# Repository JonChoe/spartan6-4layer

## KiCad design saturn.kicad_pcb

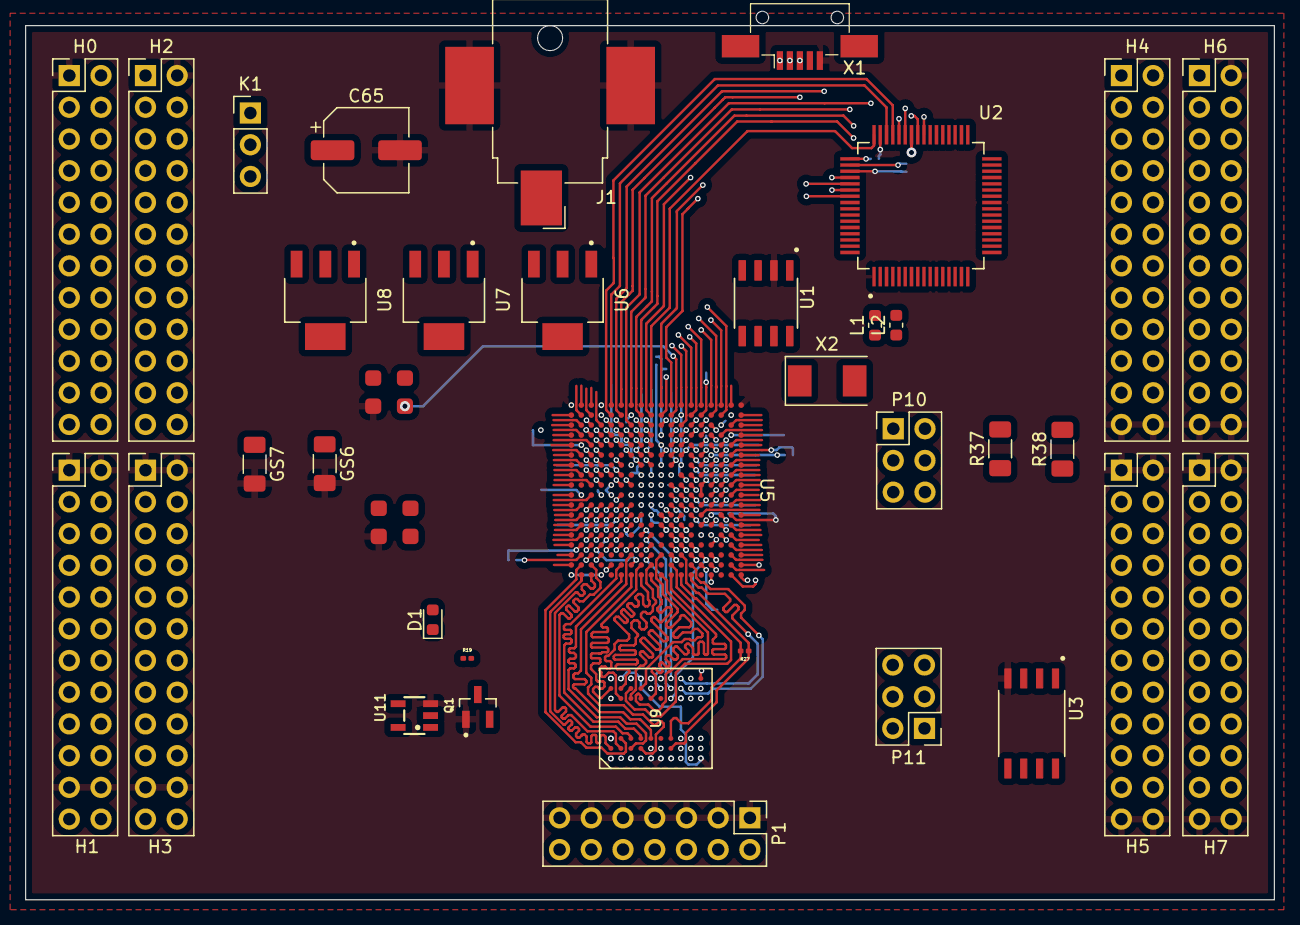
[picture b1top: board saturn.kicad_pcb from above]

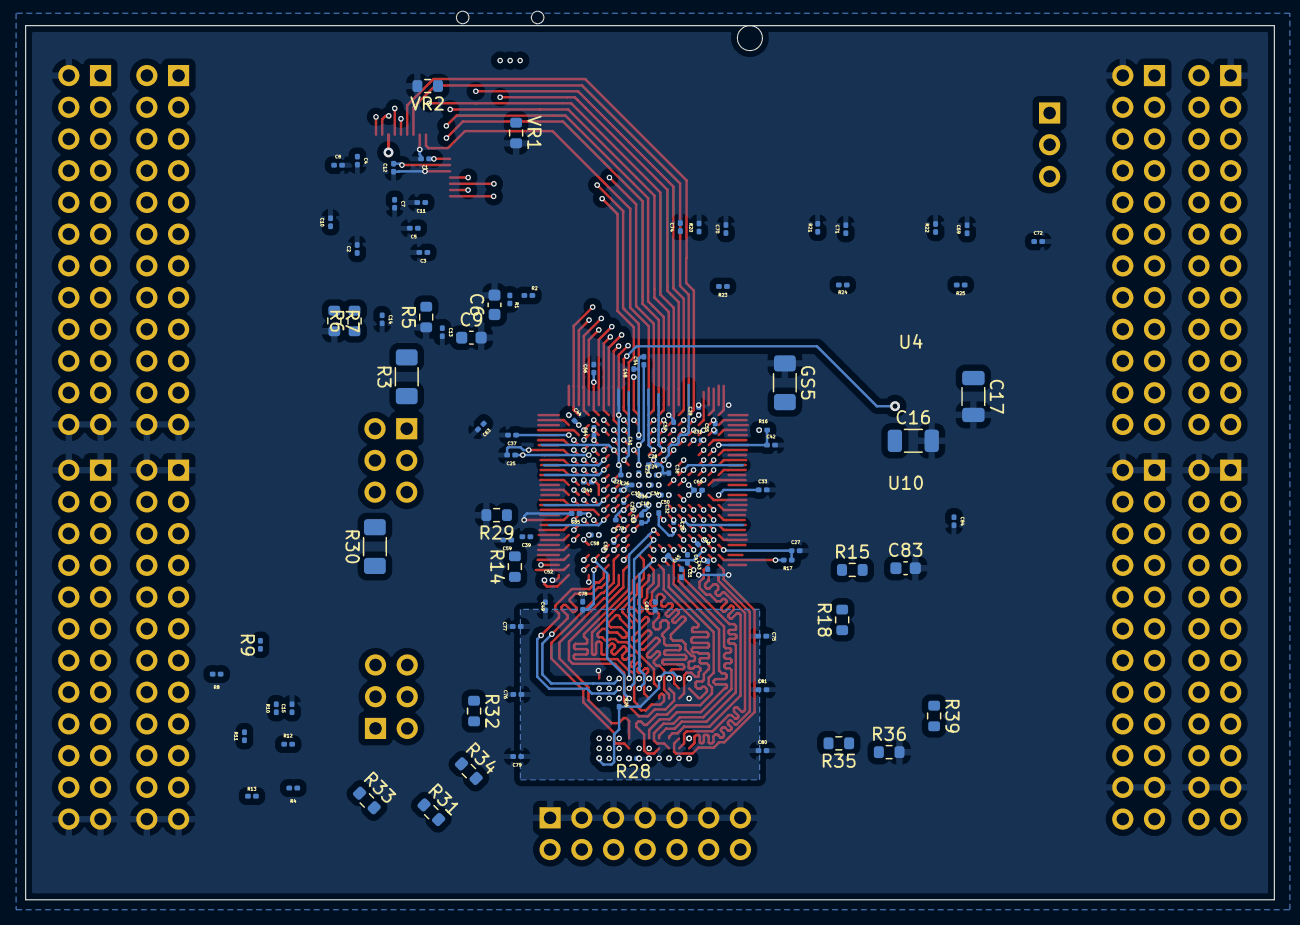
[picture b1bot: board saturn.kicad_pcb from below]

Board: 4 copper layers, 100.0 x 70.0 mm, 153 parts (116 on the bottom side), 261 nets.

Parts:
C1, C2, C3, C4, C5, C7, C8, C10, C11, C12, C13, C14, C15, C72, C73, C74, C75, C76, C77, C78, C79, C80, C81, C82: 0.1uF; C_0201_0603Metric
C6, C9: 22pF; C_0603_1608Metric
C16, C17: DNP; C_1206_3216Metric
C18, C19, C20, C21, C22, C23, C24, C25, C26, C27, C28, C29, C30, C31, C32, C33, C34, C35, C36, C37, C38, C39, C40, C41, C42, C43, C44, C45, C46, C47, C48, C49, C50, C51, C52, C53, C54, C55, C56, C57, C58, C59, C60, C63, C64, C84: 0.01uF; C_0201_0603Metric
C65: 47uF; CP_Elec_6.3x7.7
C69, C70, C71: 10uF; C_0201_0603Metric
C83: 15pF; C_0603_1608Metric
D1: LED; LED_0603_1608Metric
GS5, GS6, GS7: PAD; R_1206_3216Metric_Pad1.30x1.75mm_HandSolder
H0, H1, H2, H3, H4, H5, H6, H7: header-2x12-2.54; PinHeader_2x12_P2.54mm_Vertical
J1: DC_barrel; BarrelJack_CUI_PJ-036AH-SMT_Horizontal
K1: VBUS_VCCIN; PinHeader_1x03_P2.54mm_Vertical
L1, L2: INDUCTOR; L_0603_1608Metric
P1: JTAG-14PIN; PinHeader_2x07_P2.54mm_Vertical
P10, P11: PLUG-6-PIN; PinHeader_2x03_P2.54mm_Vertical
Q1: NPN; SOT95P237X125-3N
R1, R10, R11, R13, R16: 10K; R_0201_0603Metric
R2: 2K2; R_0201_0603Metric
R3, R30, R37, R38: DNP; R_1206_3216Metric_Pad1.30x1.75mm_HandSolder
R4, R8, R9, R12, R21: 0R; R_0201_0603Metric
R5: 12K; R_0603_1608Metric
R6: 4K7; R_0603_1608Metric
R7, R15, R35, R36: 10K; R_0603_1608Metric
R14: 4.7K; R_0603_1608Metric
R17, R19, R28: 4.7K; R_0201_0603Metric
R18: 1K; R_0603_1608Metric
R20: 330R; R_0201_0603Metric
R22, R26, R27: 100R; R_0201_0603Metric
R23, R24, R25: 220R; R_0201_0603Metric
R29: 100R; R_0603_1608Metric
R31, R32, R33, R34: 0R; R_0603_1608Metric
R39: 2.2K; R_0603_1608Metric
U1: 93LC46; SOIC127P600X175-8N
U2: FT2232H; QFP50P1200X1200X160-64N
U3: N25Q128; SOP127P790X216-8N
U4, U10: FXO-HC536R
U5: SPARTAN6-CSG324; CSG324
U6, U7, U8: LM1117-ADJ; SOT230P700X180-4N
U9: MT46H32M16LF; VFBGA60
U11: 74LVC1GU04; SOT23-5
VR1, VR2: VARIABLE_RESISTOR; R_0603_1608Metric
X1: USBMINI; USB_Mini-B_AdamTech_MUSB-B5-S-VT-TSMT-1_SMD_Vertical
X2: 12MHz; Crystal_SMD_0603-2Pin_6.0x3.5mm

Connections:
/FTDI2232H/74LV-A: R35.1, R36.1, U2.24 (ADBUS7), U11.2 (A)
/FTDI2232H/C: R4.2, U3.6 (C)
/FTDI2232H/D: R12.2, U3.5 (D)
/FTDI2232H/DM: U2.7 (DM), VR1.1, X1.2 (D-)
/FTDI2232H/DO: R1.2, R2.1, U1.1 (DO)
/FTDI2232H/DP: U2.8 (DP), VR2.1, X1.3 (D+)
/FTDI2232H/EECLK: R38.2, U1.4 (CLK), U2.62 (EECLK)
/FTDI2232H/EECS: R37.2, U1.5 (CS), U2.63 (EECS)
/FTDI2232H/EEDATA: R2.2, U1.3 (DI), U2.61 (EEDATA)
/FTDI2232H/OSCI: C6.1, U2.2 (OSCI), X2.1
/FTDI2232H/OSCO: C9.1, U2.3 (OSCO), X2.2
/FTDI2232H/Q: R9.1, U3.2 (Q)
/FTDI2232H/REF: R5.2, U2.6 (REF)
/FTDI2232H/TCK: P1.6, P11.2, P11.4, R31.1, R31.2, U2.16 (ADBUS0), U5.A17 (TCK)
/FTDI2232H/TDI: P1.10, P10.3, P10.5, R32.1, R32.2, U2.17 (ADBUS1), U5.D15 (TDI)
/FTDI2232H/TDO: P1.8, P10.2, P10.4, R34.1, R34.2, U2.18 (ADBUS2), U5.D16 (TDO)
/FTDI2232H/TMS: P1.4, P11.3, P11.5, R33.1, R33.2, U2.19 (ADBUS3), U5.B18 (TMS)
/FTDI2232H/U1-CS: P11.6, R8.2, U5.V3 (IO_L65N_CSO_B_2)
/FTDI2232H/U1-D0: U2.38 (BDBUS0), U5.L17 (IO_L46P_FCS_B_M1DQ2_1)
/FTDI2232H/U1-D1: U2.39 (BDBUS1), U5.L18 (IO_L46N_FOE_B_M1DQ3_1)
/FTDI2232H/U1-D2: U2.40 (BDBUS2), U5.M16 (IO_L47P_FWE_B_M1DQ0_1)
/FTDI2232H/U1-D3: U2.41 (BDBUS3), U5.M18 (IO_L47N_LDC_M1DQ1_1)
/FTDI2232H/U1-D4: U2.43 (BDBUS4), U5.N17 (IO_L48P_HDC_M1DQ8_1)
/FTDI2232H/U1-D5: U2.44 (BDBUS5), U5.N18 (IO_L48N_M1DQ9_1)
/FTDI2232H/U1-D6: U2.45 (BDBUS6), U5.P17 (IO_L49P_M1DQ10_1)
/FTDI2232H/U1-D7: U2.46 (BDBUS7), U5.P18 (IO_L49N_M1DQ11_1)
/FTDI2232H/U1-RD#: U2.53 (BCBUS2), U5.J18 (IO_L44N_A2_M1DQ7_1)
/FTDI2232H/U1-RXF#: U2.48 (BCBUS0), U5.K18 (IO_L45N_A0_M1LDQSN_1)
/FTDI2232H/U1-SCK: P11.1, R4.1, U5.R15 (IO_L1P_CCLK_2)
/FTDI2232H/U1-SDI: P10.1, R3.1, R9.2, U5.R13 (IO_L3P_D0_DIN_MISO_MISO1_2)
/FTDI2232H/U1-SDO: P10.6, R12.1, R30.2, U5.T13 (IO_L3N_MOSI_CSI_B_MISO0_2)
/FTDI2232H/U1-SIWUB: U2.55 (BCBUS4), U5.H18 (IO_L43N_GCLK4_M1DQ5_1)
/FTDI2232H/U1-TXE#: U2.52 (BCBUS1), U5.K17 (IO_L45P_A1_M1LDQS_1)
/FTDI2232H/U1-WR#: U2.54 (BCBUS3), U5.J16 (IO_L44P_A3_M1DQ6_1)
/FTDI2232H/VCC1V8: C1.1, C2.1, C3.1, C4.1, U2.12 (VCORE), U2.37 (VCORE), U2.49 (VREGOUT), U2.64 (VCORE)
/FTDI2232H/VPHY: C13.1, L1.2, U2.4 (VPHY)
/FTDI2232H/VPLL: C14.1, L2.2, U2.9 (VPLL)
/FTDI2232H/~HOLD: R13.2, U3.7 (~HOLD)
/FTDI2232H/~RESET: R6.2, R7.1, U2.14 (~RESET)
/FTDI2232H/~S: R8.1, R11.2, U3.1 (~S)
/FTDI2232H/~W: R10.2, U3.3 (~W)
/FTDI-AC0: H4.1, U2.26 (ACBUS0)
/FTDI-AC1: H4.2, U2.27 (ACBUS1)
/FTDI-AC2: H4.3, U2.28 (ACBUS2)
/FTDI-AC3: H4.4, U2.29 (ACBUS3)
/FTDI-AC4: H4.5, U2.30 (ACBUS4)
/FTDI-AC5: H4.6, U2.32 (ACBUS5)
/FTDI-AC6: H4.7, U2.33 (ACBUS6)
/FTDI-AC7: H4.8, U2.34 (ACBUS7)
/GPIOS/GPIO-N1: H2.3, U5.K14 (IO_L39N_M10DT_1)
/GPIOS/GPIO-N2: H0.3, U5.G13 (IO_L32N_A16_M1A9_1)
/GPIOS/GPIO-N3: H2.5, U5.H14 (IO_L36N_A8_M1BA1_1)
/GPIOS/GPIO-N4: H0.5, U5.H16 (IO_L37N_A6_M1A1_1)
/GPIOS/GPIO-N6: H0.7, U5.G14 (IO_L30N_A20_M1A11_1)
/GPIOS/GPIO-N7: H2.7, U5.G18 (IO_L38N_A4_M1CLKN_1)
/GPIOS/GPIO-N8: H0.9, U5.F16 (IO_L1N_A24_VREF_1)
/GPIOS/GPIO-N9: H2.9, U5.F18 (IO_L35N_A10_M1A2_1)
/GPIOS/GPIO-N10: H0.11, U5.E18 (IO_L33N_A14_M1A4_1)
/GPIOS/GPIO-N11: H2.11, U5.D18 (IO_L31N_A18_M1A12_1)
/GPIOS/GPIO-N12: H0.13, U5.C18 (IO_L29N_A22_M1A14_1)
/GPIOS/GPIO-N13: H6.4, U5.K13 (IO_L34N_A12_M1BA2_1)
/GPIOS/GPIO-N20: H6.6, U5.M13 (IO_L61N_1)
/GPIOS/GPIO-N21: H4.12, U5.K16 (IO_L41N_GCLK8_M1CASN_1)
/GPIOS/GPIO-N22: H6.8, U5.N14 (IO_L53N_VREF_1)
/GPIOS/GPIO-N23: H6.12, U5.N16 (IO_L50N_M1UDQSN_1)
/GPIOS/GPIO-N24: H6.10, U5.L16 (IO_L42N_GCLK6_TRDY1_M1LDM_1)
/GPIOS/GPIO-N25: H6.14, U5.P16 (IO_L74N_DOUT_BUSY_1)
/GPIOS/GPIO-N26: H4.10, U5.L13 (IO_L40N_GCLK10_M1A6_1)
/GPIOS/GPIO-N27: H4.14, U5.T18 (IO_L51N_M1DQ13_1)
/GPIOS/GPIO-N28: H6.16, U5.U18 (IO_L52N_M1DQ15_1)
/GPIOS/GPIO-N29: H2.13, U5.A16 (IO_L66N_SCP0_0)
/GPIOS/GPIO-N30: H0.15, U5.A15 (IO_L64N_SCP4_0)
/GPIOS/GPIO-N31: H2.15, U5.C14 (IO_L65N_SCP2_0)
/GPIOS/GPIO-N32: H0.17, U5.A14 (IO_L62N_VREF_0)
/GPIOS/GPIO-N33: H2.17, U5.E13 (IO_L63N_SCP6_0)
/GPIOS/GPIO-N34: H0.19, U5.A13 (*IO_L50N_0)
/GPIOS/GPIO-N35: H2.19, U5.E12 (IO_L51N_0)
/GPIOS/GPIO-N36: H0.21, U5.C12 (*IO_L47N_0)
/GPIOS/GPIO-N37: H2.21, U5.A12 (IO_L41N_0)
/GPIOS/GPIO-N38: H0.23, U5.E11 (*IO_L42N_0)
/GPIOS/GPIO-N39: H1.3, U5.F10 (*IO_L40N_0)
/GPIOS/GPIO-N40: H2.23, U5.C11 (IO_L36N_GCLK14_0)
/GPIOS/GPIO-N41: H3.3, U5.A11 (IO_L39N_0)
/GPIOS/GPIO-N42: H1.5, U5.A10 (IO_L37N_GCLK12_0)
/GPIOS/GPIO-N43: H3.5, U5.F9 (IO_L38N_VREF_0)
/GPIOS/GPIO-N44: H1.7, U5.C9 (IO_L34N_GCLK18_0)
/GPIOS/GPIO-N45: H3.7, U5.A9 (IO_L35N_GCLK16_0)
/GPIOS/GPIO-N46: H1.9, U5.F8 (*IO_L32N_0)
/GPIOS/GPIO-N47: H3.9, U5.E8 (*IO_L9N_0)
/GPIOS/GPIO-N48: H1.11, U5.C8 (IO_L11N_0)
/GPIOS/GPIO-N49: H3.11, U5.A8 (IO_L33N_0)
/GPIOS/GPIO-N50: H1.13, U5.E6 (*IO_L7N_0)
/GPIOS/GPIO-N51: H3.13, U5.A7 (IO_L10N_0)
/GPIOS/GPIO-N52: H1.15, U5.A6 (IO_L8N_VREF_0)
/GPIOS/GPIO-N53: H3.15, U5.C6 (IO_L3N_0)
/GPIOS/GPIO-N54: H1.17, U5.A5 (IO_L6N_0)
/GPIOS/GPIO-N55: H3.17, U5.A4 (IO_L5N_0)
/GPIOS/GPIO-N56: H1.19, U5.A3 (IO_L4N_0)
/GPIOS/GPIO-N57: H3.19, U5.A2 (IO_L2N_0)
/GPIOS/GPIO-N58: H4.16, U5.V16 (IO_L2N_CMPMOSI_2)
/GPIOS/GPIO-N59: H6.18, U5.V15 (*IO_L5N_2)
/GPIOS/GPIO-N60: H4.18, U5.V14 (IO_L12N_D2_MISO3_2)
/GPIOS/GPIO-N61: H6.20, U5.V13 (IO_L14N_D12_2)
/GPIOS/GPIO-N62: H4.20, U5.V12 (*IO_L19N_2)
/GPIOS/GPIO-N63: H6.22, U5.N11 (*IO_L15N_2)
/GPIOS/GPIO-N64: H4.22, U5.T11 (IO_L16N_VREF_2)
/GPIOS/GPIO-N65: H7.4, U5.V11 (IO_L23N_2)
/GPIOS/GPIO-N66: H5.4, U5.P11 (*IO_L20N_2)
/GPIOS/GPIO-N67: H7.6, U5.N9 (*IO_L22N_2)
/GPIOS/GPIO-N68: H5.6, U5.T10 (IO_L29N_GCLK2_2)
/GPIOS/GPIO-N69: H7.8, U5.T8 (IO_L31N_GCLK30_D15_2)
/GPIOS/GPIO-N70: H5.8, U5.V9 (IO_L32N_GCLK28_2)
/GPIOS/GPIO-N71: H7.10, U5.N8 (*IO_L40N_2)
/GPIOS/GPIO-N72: H5.10, U5.P8 (*IO_L44N_2)
/GPIOS/GPIO-N73: H7.12, U5.V8 (IO_L41N_VREF_2)
/GPIOS/GPIO-N74: H7.14, U5.P7 (*IO_L47N_2)
/GPIOS/GPIO-N75: H5.12, U5.V7 (IO_L43N_2)
/GPIOS/GPIO-N76: H5.14, U5.T7 (IO_L46N_2)
/GPIOS/GPIO-N77: H7.16, U5.V6 (IO_L45N_2)
/GPIOS/GPIO-N78: H5.16, U5.P6 (IO_L64N_D9_2)
/GPIOS/GPIO-N79: H5.18, U5.T5 (IO_L48N_RDWR_B_VREF_2)
/GPIOS/GPIO-N80: H7.18, U5.V5 (IO_L49N_D4_2)
/GPIOS/GPIO-N81: H7.20, U5.V4 (IO_L63N_2)
/GPIOS/GPIO-N82: H5.20, U5.T3 (IO_L62N_D6_2)
/GPIOS/GPIO-P1: H2.4, U5.J13 (IO_L39P_M1A3_1)
/GPIOS/GPIO-P2: H0.4, U5.H12 (IO_L32P_A17_M1A8_1)
/GPIOS/GPIO-P3: H2.6, U5.H13 (IO_L36P_A9_M1BA0_1)
/GPIOS/GPIO-P4: H0.6, U5.H15 (IO_L37P_A7_M1A0_1)
/GPIOS/GPIO-P6: H0.8, U5.F14 (IO_L30P_A21_M1RESET_1)
/GPIOS/GPIO-P7: H2.8, U5.G16 (IO_L38P_A5_M1CLK_1)
/GPIOS/GPIO-P8: H0.10, U5.F15 (IO_L1P_A25_1)
/GPIOS/GPIO-P9: H2.10, U5.F17 (IO_L35P_A11_M1A7_1)
/GPIOS/GPIO-P10: H0.12, U5.E16 (IO_L33P_A15_M1A10_1)
/GPIOS/GPIO-P11: H2.12, U5.D17 (IO_31P_A19_M1CKE_1)
/GPIOS/GPIO-P12: H0.14, U5.C17 (IO_L29P_A23_M1A13_1)
/GPIOS/GPIO-P13: H6.3, U5.K12 (IO_L34P_A13_M1WE_1)
/GPIOS/GPIO-P20: H6.5, U5.L14 (IO_L61P_1)
/GPIOS/GPIO-P21: H4.11, U5.K15 (IO_L41P_GCLK9_IRDY1_M1RASN_1)
/GPIOS/GPIO-P22: H6.7, U5.M14 (IO_L53P_1)
/GPIOS/GPIO-P23: H6.11, U5.N15 (IO_L50P_M1UDQS_1)
/GPIOS/GPIO-P24: H6.9, U5.L15 (IO_L42P_GCLK7_M1UDM_1)
/GPIOS/GPIO-P25: H6.13, U5.P15 (IO_L74P_AWAKE_1)
/GPIOS/GPIO-P26: H4.9, U5.L12 (IO_L40P_GCLK11_M1A5_1)
/GPIOS/GPIO-P27: H4.13, U5.T17 (IO_L51P_M1DQ12_1)
/GPIOS/GPIO-P28: H6.15, U5.U17 (IO_L52P_M1DQ14_1)
/GPIOS/GPIO-P29: H2.14, U5.B16 (IO_L66P_SCP1_0)
/GPIOS/GPIO-P30: H0.16, U5.C15 (IO_L64P_SCP5_0)
/GPIOS/GPIO-P31: H2.16, U5.D14 (IO_L65P_SCP3_0)
/GPIOS/GPIO-P32: H0.18, U5.B14 (IO_L62P_0)
/GPIOS/GPIO-P33: H2.18, U5.F13 (IO_L63P_SCP7_0)
/GPIOS/GPIO-P34: H0.20, U5.C13 (*IO_L50P_0)
/GPIOS/GPIO-P35: H2.20, U5.F12 (IO_L51P_0)
/GPIOS/GPIO-P36: H0.22, U5.D12 (*IO_L47P_0)
/GPIOS/GPIO-P37: H2.22, U5.B12 (IO_L41P_0)
/GPIOS/GPIO-P38: H0.24, U5.F11 (*IO_L42P_0)
/GPIOS/GPIO-P39: H1.4, U5.G11 (*IO_L40P_0)
/GPIOS/GPIO-P40: H2.24, U5.D11 (IO_L36P_GCLK15_0)
/GPIOS/GPIO-P41: H3.4, U5.B11 (IO_L39P_0)
/GPIOS/GPIO-P42: H1.6, U5.C10 (IO_L37P_GCLK13_0)
/GPIOS/GPIO-P43: H3.6, U5.G9 (IO_L38P_0)
/GPIOS/GPIO-P44: H1.8, U5.D9 (IO_L34P_GCLK19_0)
/GPIOS/GPIO-P45: H3.8, U5.B9 (IO_L35P_GCLK17_0)
/GPIOS/GPIO-P46: H1.10, U5.G8 (*IO_L32P_0)
/GPIOS/GPIO-P47: H3.10, U5.E7 (*IO_L9P_0)
/GPIOS/GPIO-P48: H1.12, U5.D8 (IO_L11P_0)
/GPIOS/GPIO-P49: H3.12, U5.B8 (IO_L33P_0)
/GPIOS/GPIO-P50: H1.14, U5.F7 (*IO_L7P_0)
/GPIOS/GPIO-P51: H3.14, U5.C7 (IO_L10P_0)
/GPIOS/GPIO-P52: H1.16, U5.B6 (IO_L8P_0)
/GPIOS/GPIO-P53: H3.16, U5.D6 (IO_L3P_0)
/GPIOS/GPIO-P54: H1.18, U5.C5 (IO_L6P_0)
/GPIOS/GPIO-P55: H3.18, U5.B4 (IO_L5P_0)
/GPIOS/GPIO-P56: H1.20, U5.B3 (IO_L4P_0)
/GPIOS/GPIO-P57: H3.20, U5.B2 (IO_L2P_0)
/GPIOS/GPIO-P58: H4.15, U5.U16 (IO_L2P_CMPCLK_2)
/GPIOS/GPIO-P59: H6.17, U5.U15 (*IO_L5P_2)
/GPIOS/GPIO-P60: H4.17, U5.T14 (IO_L12P_D1_MISO2_2)
/GPIOS/GPIO-P61: H6.19, U5.U13 (IO_L14P_D11_2)
/GPIOS/GPIO-P62: H4.19, U5.T12 (*IO_L19P_2)
/GPIOS/GPIO-P63: H6.21, U5.M11 (*IO_L15P_2)
/GPIOS/GPIO-P64: H4.21, U5.R11 (IO_L16P_2)
/GPIOS/GPIO-P65: H7.3, U5.U11 (IO_L23P_2)
/GPIOS/GPIO-P66: H5.3, U5.N10 (*IO_L20P_N)
/GPIOS/GPIO-P67: H7.5, U5.M10 (*IO_L22P_2)
/GPIOS/GPIO-P68: H5.5, U5.R10 (IO_L29P_GCLK3_2)
/GPIOS/GPIO-P69: H7.7, U5.R8 (IO_L31P_GCLK31_D14_2)
/GPIOS/GPIO-P70: H5.7, U5.T9 (IO_L32P_GCLK29_2)
/GPIOS/GPIO-P71: H7.9, U5.M8 (*IO_L40P_2)
/GPIOS/GPIO-P72: H5.9, U5.N7 (*IO_L44P_2)
/GPIOS/GPIO-P73: H7.11, U5.U8 (IO_L41P_2)
/GPIOS/GPIO-P74: H7.13, U5.N6 (*IO_L47P_2)
/GPIOS/GPIO-P75: H5.11, U5.U7 (IO_L43P_2)
/GPIOS/GPIO-P76: H5.13, U5.R7 (IO_L46P_2)
/GPIOS/GPIO-P77: H7.15, U5.T6 (IO_L45P_2)
/GPIOS/GPIO-P78: H5.15, U5.N5 (IO_L64P_D8_2)
/GPIOS/GPIO-P79: H5.17, U5.R5 (IO_L48P_D7_2)
/GPIOS/GPIO-P80: H7.17, U5.U5 (IO_L49P_D3_2)
/GPIOS/GPIO-P81: H7.19, U5.T4 (IO_L63P_2)
/GPIOS/GPIO-P82: H5.19, U5.R3 (IO_L62P_D5_2)
/POWER/1: C65.1, J1.1, K1.3
/POWER/ADJ: R20.1, R21.1, R22.1, R23.2, R24.2, R25.2, U6.1 (ADJ), U7.1 (ADJ), U8.1 (ADJ)
/RAM/CS#: R26.1, U9.H7 (CS#)
/RAM/DDR-A0: U5.J7 (IO_L47P_M3A0_3), U9.J8 (A0)
/RAM/DDR-A1: U5.J6 (IO_L47N_M3A1_3), U9.J9 (A1)
/RAM/DDR-A2: U5.H5 (IO_L49N_M3A2_3), U9.K7 (A2)
/RAM/DDR-A3: U5.L7 (IO_L45P_H3A3_3), U9.K8 (A3)
/RAM/DDR-A4: U5.F3 (IO_L51N_M3A4_3), U9.K2 (A4)
/RAM/DDR-A5: U5.H4 (IO_L44P_GCLK21_M3A5_3), U9.K3 (A5)
/RAM/DDR-A6: U5.H3 (IO_L44N_GCLK20_M3A6_3), U9.J1 (A6)
/RAM/DDR-A7: U5.H6 (IO_L49P_M3A7_3), U9.J2 (A7)
/RAM/DDR-A8: U5.D2 (IO_L52P_M3A8_3), U9.J3 (A8)
/RAM/DDR-A9: U5.D1 (IO_L52N_M3A9_3), U9.H1 (A9)
/RAM/DDR-A10: U5.F4 (IO_L51P_M3A10_3), U9.J7 (A10)
/RAM/DDR-A11: U5.D3 (IO_L54N_M3A11_3), U9.H2 (A11)
/RAM/DDR-A12: U5.G6 (IO_L53N_M3A12_3), U9.H3 (A12)
/RAM/DDR-BA0: U5.F2 (IO_L48P_M3BA0_3), U9.H8 (BA0)
/RAM/DDR-BA1: U5.F1 (IO_L48N_M3BA1_3), U9.H9 (BA1)
/RAM/DDR-CAS: U5.K5 (IO_L43N_GCLK22_IRDY2_M3CASN_3), U9.G8 (CAS#)
/RAM/DDR-CKE: R28.2, U5.H7 (IO_L53P_M3CKE_3), U9.G1 (CKE)
/RAM/DDR-CK_N: R27.2, U5.G1 (IO_L46N_M3CLKN_3), U9.G3 (CK#)
/RAM/DDR-CK_P: R27.1, U5.G3 (IO_L46P_M3CLK_3), U9.G2 (CK)
/RAM/DDR-D0: U5.L2 (IO_L37P_M3DQ0_3), U9.A8 (DQ0)
/RAM/DDR-D1: U5.L1 (IO_L37N_M3DQ1_3), U9.B7 (DQ1)
/RAM/DDR-D2: U5.K2 (IO_L38P_M3DQ2_3), U9.B8 (DQ2)
/RAM/DDR-D3: U5.K1 (IO_L38N_M3DQ3_3), U9.C7 (DQ3)
/RAM/DDR-D4: U5.H2 (IO_L41P_GCLK27_M3DQ4_3), U9.C8 (DQ4)
/RAM/DDR-D5: U5.H1 (IO_L41N_GCLK26_M3DQ5_3), U9.D7 (DQ5)
/RAM/DDR-D6: U5.J3 (IO_L40P_M3DQ6_3), U9.D8 (DQ6)
/RAM/DDR-D7: U5.J1 (IO_L40N_M3DQ7_3), U9.E7 (DQ7)
/RAM/DDR-D8: U5.M3 (IO_L36P_M3DQ8_3), U9.E3 (DQ8)
/RAM/DDR-D9: U5.M1 (IO_L36N_M3DQ9_3), U9.D2 (DQ9)
/RAM/DDR-D10: U5.N2 (IO_L35P_M3DQ10_3), U9.D3 (DQ10)
/RAM/DDR-D11: U5.N1 (IO_L35N_M3DQ11_3), U9.C2 (DQ11)
/RAM/DDR-D12: U5.T2 (IO_L33P_M3DQ12_3), U9.C3 (DQ12)
/RAM/DDR-D13: U5.T1 (IO_L33N_M3DQ13_3), U9.B2 (DQ13)
/RAM/DDR-D14: U5.U2 (IO_L32P_M3DQ14_3), U9.B3 (DQ14)
/RAM/DDR-D15: U5.U1 (IO_L32N_M3DQ15_3), U9.A2 (DQ15)
/RAM/DDR-LDM: U5.K3 (IO_L42N_GCLK24_M3LDM_3), U9.F8 (LDM)
/RAM/DDR-LDQS: U5.L4 (IO_L39P_M3LDQS_3), U9.E8 (LDQS)
/RAM/DDR-RAS: U5.L5 (IO_L43P_GCLK23_M3RASN_3), U9.G9 (RAS#)
/RAM/DDR-UDM: U5.K4 (IO_L42P_GCLK25_TRDY2_M3UDM_3), U9.F2 (UDM)
/RAM/DDR-UDQS: U5.P2 (IO_L34P_M3UDQS_3), U9.E2 (UDQS)
/RAM/DDR-WE: U5.E3 (IO_L50P_M3WE_3), U9.G7 (WE#)
/RAM/RZQ: R29.1, U5.N4 (IO_L1P_3)
/SPARTAN6/DONE: R18.2, U5.V17 (DONE_2)
/SPARTAN6/GCLK1: C83.1, U5.V10 (IO_L30N_GCLK0_USERCCLK_2), U10.3 (OUT)
/SPARTAN6/GCLK2: C16.1, U4.3 (OUT), U5.H17 (IO_L42P_GCLK5_M1DQ4_1)
/SPARTAN6/HSWAP: R14.2, U5.D4 (IO_l1P_HSWAPEN_0)
/SPARTAN6/INIT_B: H5.21, R17.2, U5.U3 (IO_L65P_INIT_B_2)
/SPARTAN6/M0: GS6.1, R16.1, U5.T15 (IO_L1N_M0_CMPMISO_2)
/SPARTAN6/M1: GS7.1, R15.1, U5.N12 (IO_L13P_M1_2)
/SPARTAN6/PROG: H7.21, Q1.3 (C), R19.2, R39.1, U5.V2 (PROGRAM_B_2), U11.4 (Y)
/SPARTAN6/SUSPEND: GS5.2, U5.R16 (SUSPEND)
DDR1V8: C43.1, C45.1, C47.1, C49.1, C51.1, C53.1, C75.1, C76.1, C77.1, C78.1, C79.1, C80.1, C81.1, C82.1, U5.E2 (VCCO_3), U5.G4 (VCCO_3), U5.J2 (VCCO_3), U5.J5 (VCCO_3), U5.M4 (VCCO_3), U5.R2 (VCCO_3), U9.A7 (VDDQ), U9.A9 (VDD), U9.B1 (VDDQ), U9.C9 (VDDQ), U9.D1 (VDDQ), U9.E9 (VDDQ), U9.F9 (VDD), U9.K9 (VDD)
GND: C1.2, C2.2, C3.2, C4.2, C5.2, C6.2, C7.2, C8.2, C9.2, C10.2, C11.2, C12.1, C13.2, C14.2, C15.2, C16.2, C17.2, C18.2, C19.2, C20.2, C21.2, C22.2, C23.2, C24.2, C25.2, C26.2, C27.2, C28.2, C29.2, C30.2, C31.2, C32.2, C33.2, C34.2, C35.2, C36.2, C37.2, C38.2, C39.2, C40.2, C41.2, C42.2, C43.2, C44.2, C45.2, C46.2, C47.2, C48.2, C49.2, C50.2, C51.2, C52.2, C53.2, C54.2, C55.2, C56.2, C57.2, C58.2, C59.2, C60.2, C63.2, C64.2, C65.2, C69.2, C70.2, C71.2, C72.2, C73.2, C74.2, C75.2, C76.2, C77.2, C78.2, C79.2, C80.2, C81.2, C82.2, C83.2, C84.2, GS5.1, GS6.2, GS7.2, H0.1, H1.1, H1.2, H1.21, H1.22, H2.2, H3.1, H3.2, H3.21, H3.22, H4.23, H4.24, H5.1, H5.2, H5.23, H5.24, H6.2, H6.23, H6.24, H7.1, H7.2, H7.23, H7.24, J1.2, J1.3, P1.1, P1.3, P1.5, P1.7, P1.9, P1.11, P1.13, Q1.1 (E), R5.1, R7.2, R20.2, R21.2, R22.2, R26.2, R28.1, R29.2, R36.2, U1.2 (GND), U2.1 (GND), U2.5 (GND), U2.10 (AGND), U2.11 (GND), U2.13 (TEST), U2.15 (GND), U2.25 (GND), U2.35 (GND), U2.47 (GND), U2.51 (GND), U3.4 (VSS), U4.2 (GND), U5.A1 (GND), U5.A18 (GND), U5.B7 (GND), U5.B13 (GND), U5.C3 (GND), U5.C16 (GND), U5.D5 (GND), U5.D10 (GND), U5.E15 (GND), U5.G2 (GND), U5.G5 (GND), U5.G12 (GND), U5.G17 (GND), U5.H8 (GND), U5.H10 (GND), U5.J4 (GND), U5.J9 (GND), U5.J11 (GND), U5.J15 (GND), U5.K8 (GND), U5.K10 (GND), U5.L9 (GND), U5.L11 (GND), U5.M2 (GND), U5.M6 (GND), U5.M17 (GND), U5.N13 (GND), U5.R1 (GND), U5.R4 (GND), U5.R9 (GND), U5.R14 (GND), U5.R18 (GND), U5.T16 (GND), U5.U6 (GND), U5.U12 (GND), U5.V1 (GND), U5.V18 (GND), U9.A1 (VSS), U9.A3 (VSSQ), U9.B9 (VSSQ), U9.C1 (VSSQ), U9.D9 (TEST), U9.E1 (VSSQ), U9.F1 (VSS), U9.K1 (VSS), U10.2 (GND), U11.3 (GND), VR1.2, VR2.2, X1.5 (GND)
unnamed: D1.1 (K), R18.1
unnamed: Q1.2 (B), R35.2
VBUS: K1.1, X1.1 (VUSB)
VCC1V2: C18.1, C20.1, C22.1, C24.1, C26.1, C28.1, C30.1, C32.1, C34.1, C36.1, C38.1, C69.1, C70.1, C71.1, C72.1, C73.1, C74.1, R23.1, R24.1, R25.1, U5.G7 (VCCINT), U5.H9 (VCCINT), U5.H11 (VCCINT), U5.J8 (VCCINT), U5.J10 (VCCINT), U5.K9 (VCCINT), U5.K11 (VCCINT), U5.L8 (VCCINT), U5.L10 (VCCINT), U5.M7 (VCCINT), U5.M12 (VCCINT), U6.2 (VO), U7.2 (VO), U8.2 (VO)
VCC3V3: C5.1, C7.1, C8.1, C10.1, C11.1, C12.2, C15.1, C17.1, C19.1, C21.1, C23.1, C25.1, C27.1, C29.1, C31.1, C33.1, C35.1, C37.1, C39.1, C40.1, C41.1, C42.1, C44.1, C46.1, C48.1, C50.1, C52.1, C54.1, C55.1, C56.1, C57.1, C58.1, C59.1, C60.1, C63.1, C64.1, C84.1, D1.2 (A), H0.2, H1.23, H1.24, H3.23, H3.24, H5.22, H6.1, H7.22, L1.1, L2.1, P1.2, R1.1, R3.2, R6.1, R10.1, R11.1, R13.1, R14.1, R15.2, R16.2, R17.1, R19.1, R30.1, R37.1, R38.1, R39.2, U1.6 (VCC), U2.20 (VCCIO), U2.31 (VCCIO), U2.42 (VCCIO), U2.50 (VREGIN), U2.56 (VCCIO), U3.8 (VCC), U4.1 (E/D), U4.4 (VCC), U5.B1 (VCCAUX), U5.B5 (VCCO_0), U5.B10 (VCCO_0), U5.B15 (VCCO_0), U5.B17 (VCCAUX), U5.D7 (VCCO_0), U5.D13 (VCCO_0), U5.E5 (VCCAUX), U5.E9 (VCCAUX), U5.E10 (VCCO_0), U5.E14 (VCCAUX), U5.E17 (VCCO_1), U5.G10 (VCCAUX), U5.G15 (VCCO_1), U5.J12 (VCCAUX), U5.J14 (VCCO_1), U5.J17 (VCCO_1), U5.K7 (VCCAUX), U5.M9 (VCCAUX), U5.M15 (VCCO_1), U5.P5 (VCCAUX), U5.P9 (VCCO_2), U5.P10 (VCCAUX), U5.P14 (VCCAUX), U5.R6 (VCCO_2), U5.R12 (VCCO_2), U5.R17 (VCCO_1), U5.U4 (VCCO_2), U5.U9 (VCCO_2), U5.U14 (VCCO_2), U10.1 (E/D), U10.4 (VCC), U11.5 (VCC)
VCCIN: H2.1, K1.2, U6.3 (VI), U7.3 (VI), U8.3 (VI)

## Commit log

2024-02-10 add .gitignore and kicad project files
2024-02-10 add saturn library submodule
2024-02-10 removed libraries folder
2024-02-11 update saturn library
2024-02-11 update library
2024-02-11 update saturn-library commit
2024-02-11 update saturn-library submodule
